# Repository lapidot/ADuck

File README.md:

# ADuck

## ADuck is a split, reversible, keyboard PCB based on the A.Dux by Tapi,
## NS is the NonSplit version (that requires diodes)

## KingArthur is the exact same split, but with different silk print

## If you like this make sure to check out Tapi's crazy boards, and particularly the A.Dux on which the ADuck is based:
https://github.com/tapioki/cephalopoda/tree/main/Architeuthis%20dux
A Duck (Left) vs the A.Dux (Right)
Notice the pinkey stagger, and TRRS jack position:

## All done using ErgoGen by MrZealot
https://zealot.hu/ergogen/#

Use the YAML files as input to reproduce the boards, and edit them to your hearts content

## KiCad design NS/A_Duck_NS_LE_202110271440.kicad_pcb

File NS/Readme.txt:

This is a NON Split version of the ADuck
It's not 100% identical, but very simmilar

MCU facing downward
two optional switches in the 'tucky' thumb positions
one reset switch
pins for optional OLED

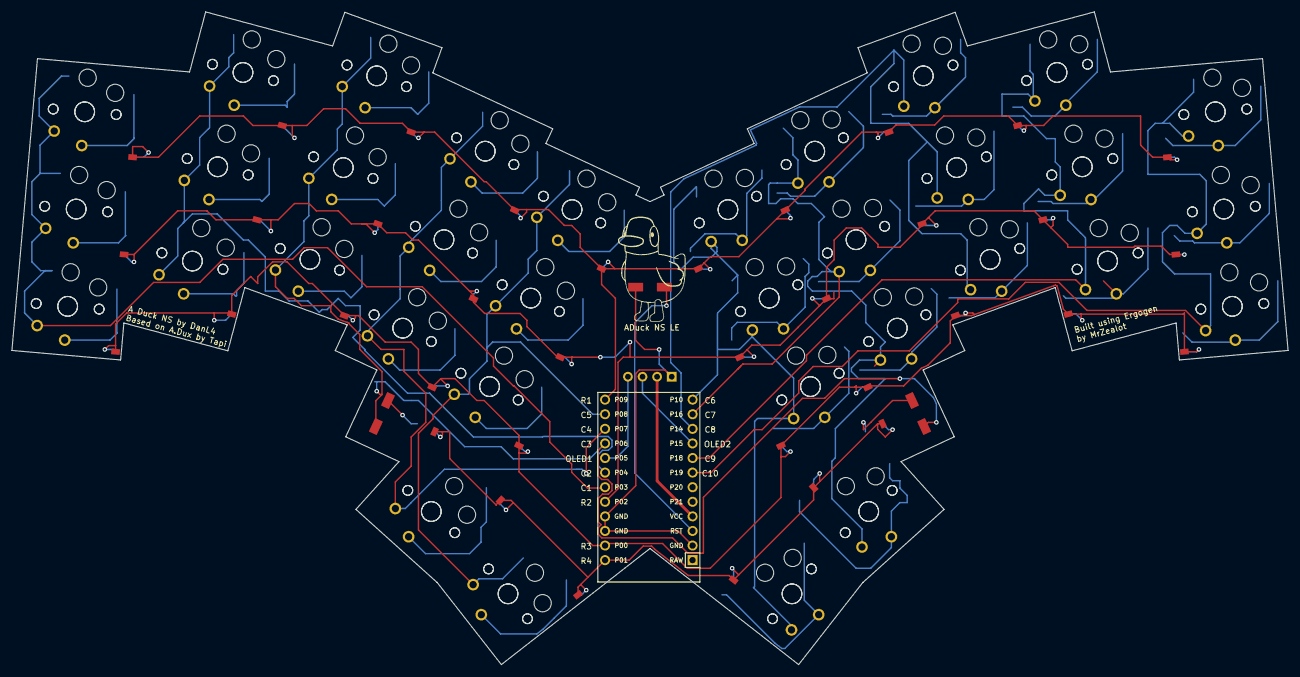
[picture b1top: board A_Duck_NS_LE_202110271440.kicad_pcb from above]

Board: 2 copper layers, 222.2 x 113.6 mm, 109 parts (0 on the bottom side), 55 nets.

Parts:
D1, D2, D3, D4, D5, D6, D7, D8, D9, D10, D11, D12, D13, D14, D15, D16, D17, D18, D19, D20, D21, D22, D23, D24, D25, D26, D27, D28, D29, D30, D31, D32, D33, D34, D35, D36: ComboDiode
J1: ADuck NS LE; Jumper
J2, J3: BigButton; Jumper
MCU1: ProMicro
OLED1: OLED; OLED_headers
S1, S2, S3, S4, S5, S6, S7, S8, S9, S10, S11, S12, S13, S14, S15, S16, S17, S18, S19, S20, S21, S22, S23, S24, S25, S26, S27, S28, S29, S30, S31, S32, S33, S34, S35, S36, S37, S38, S39, S40, S41, S42, S43, S44, S45, S46, S47, S48, S49, S50, S51, S52, S53, S54, S55, S56, S57, S58, S59, S60, S61, S62, S63, S64, S65, S66, S67, S68: PG1350

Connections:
=doideswitch: D35.2, J2.2
=doideswitchmirr: D36.2, J3.2
GND: J1.1, MCU1.2, MCU1.15, MCU1.16, OLED1.1
P0: D3.1, D6.1, D9.1, D12.1, D15.1, D20.1, D23.1, D26.1, D29.1, D32.1, MCU1.14
P1: D1.1, D2.1, D18.1, D19.1, D35.1, D36.1, MCU1.13
P2: D4.1, D7.1, D10.1, D13.1, D16.1, D21.1, D24.1, D27.1, D30.1, D33.1, MCU1.17
P3: MCU1.18, S5.1, S6.1, S7.1, S8.1, S9.1, S10.1
P4: MCU1.19, S11.1, S12.1, S13.1, S14.1, S15.1, S16.1
P5: MCU1.20, OLED1.4
P6: J2.1, J3.1, MCU1.21, S17.1, S18.1, S19.1, S20.1, S21.1, S22.1
P7: MCU1.22, S1.1, S2.1, S23.1, S24.1, S25.1, S26.1, S27.1, S28.1
P8: MCU1.23, S3.1, S4.1, S29.1, S30.1, S31.1, S32.1, S33.1, S34.1
P9: D5.1, D8.1, D11.1, D14.1, D17.1, D22.1, D25.1, D28.1, D31.1, D34.1, MCU1.24
P10: MCU1.12, S37.1, S38.1, S63.1, S64.1, S65.1, S66.1, S67.1, S68.1
P14: MCU1.10, S51.1, S52.1, S53.1, S54.1, S55.1, S56.1
P15: MCU1.9, OLED1.3
P16: MCU1.11, S35.1, S36.1, S57.1, S58.1, S59.1, S60.1, S61.1, S62.1
P18: MCU1.8, S45.1, S46.1, S47.1, S48.1, S49.1, S50.1
P19: MCU1.7, S39.1, S40.1, S41.1, S42.1, S43.1, S44.1
RST: J1.2, MCU1.3
VCC: MCU1.4, OLED1.2
home_thumb: D2.2, S3.2, S4.2
index_bottom: D12.2, S23.2, S24.2
index_home: D13.2, S25.2, S26.2
index_top: D14.2, S27.2, S28.2
inner_bottom: D15.2, S29.2, S30.2
inner_home: D16.2, S31.2, S32.2
inner_top: D17.2, S33.2, S34.2
middle_bottom: D9.2, S17.2, S18.2
middle_home: D10.2, S19.2, S20.2
middle_top: D11.2, S21.2, S22.2
mirror_home_thumb: D19.2, S37.2, S38.2
mirror_index_bottom: D29.2, S57.2, S58.2
mirror_index_home: D30.2, S59.2, S60.2
mirror_index_top: D31.2, S61.2, S62.2
mirror_inner_bottom: D32.2, S63.2, S64.2
mirror_inner_home: D33.2, S65.2, S66.2
mirror_inner_top: D34.2, S67.2, S68.2
mirror_middle_bottom: D26.2, S51.2, S52.2
mirror_middle_home: D27.2, S53.2, S54.2
mirror_middle_top: D28.2, S55.2, S56.2
mirror_near_thumb: D18.2, S35.2, S36.2
mirror_pinky_bottom: D20.2, S39.2, S40.2
mirror_pinky_home: D21.2, S41.2, S42.2
mirror_pinky_top: D22.2, S43.2, S44.2
mirror_ring_bottom: D23.2, S45.2, S46.2
mirror_ring_home: D24.2, S47.2, S48.2
mirror_ring_top: D25.2, S49.2, S50.2
near_thumb: D1.2, S1.2, S2.2
pinky_bottom: D3.2, S5.2, S6.2
pinky_home: D4.2, S7.2, S8.2
pinky_top: D5.2, S9.2, S10.2
ring_bottom: D6.2, S11.2, S12.2
ring_home: D7.2, S13.2, S14.2
ring_top: D8.2, S15.2, S16.2

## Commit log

2021-11-08 Added Gerber files, PCB files, and YAML
2021-11-08 Create JS files edited for ergogen
2021-11-08 Adding the original (king arthur) Silk Print gerber files
2021-11-09 Added YAML files
2021-11-09 Added ADuck vs ADux image
2021-11-09 Added images to readme.md
2021-11-19 Added QMK files
2021-11-20 This one actually works (plus combined GUI_F with Arrow layer)
2021-11-22 Added non split photo
2022-11-28 QMK keymap for 34 key boards (NS actually has two exra ones, so it won't work as is)
    just add two more keys to each layer or edit the .h file to remove those two unnecessary and barely usable 'keys'
2024-06-12 Added 3D Case for ADuck NS
    The case has one issue with right pinky bottom key - it doesn't have enough space for the keycap. It needed trimming. I'll fix it eventually and upload the file
2024-06-12 Rename ADuckNS35.stl to ADuckNS/Case-3D/ADuckNS35.stl
